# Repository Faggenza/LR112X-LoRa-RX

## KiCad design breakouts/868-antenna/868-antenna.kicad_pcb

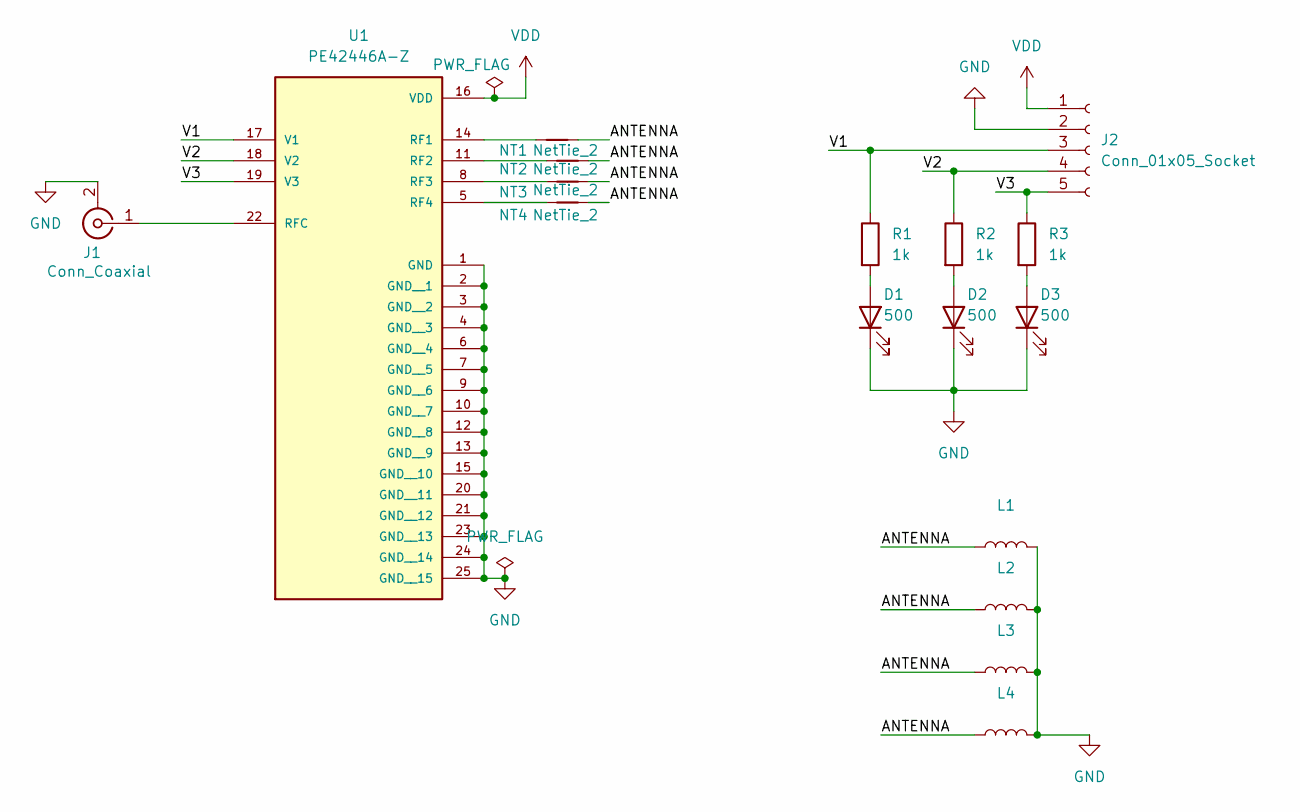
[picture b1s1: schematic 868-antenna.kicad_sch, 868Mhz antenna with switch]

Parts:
D1, D2, D3: 500; LED_0805_2012Metric_Pad1.15x1.40mm_HandSolder
J1: Conn_Coaxial; SMA_Amphenol_901-144_Vertical
J2: Conn_01x05_Socket; PinSocket_1x05_P2.54mm_Vertical
L1, L2, L3, L4: L_0805_2012Metric_Pad1.05x1.20mm_HandSolder
NT1, NT2, NT3, NT4: NetTie_2; NetTie-2_SMD_Pad0.5mm
R1, R2, R3: 1k; R_0805_2012Metric_Pad1.20x1.40mm_HandSolder
U1: PE42446A-Z; IC_PE42446A-Z; PARTREV 08/2024

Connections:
/ANTENNA: L1.1, L2.1, L3.1, L4.1, NT1.2, NT2.2, NT3.2, NT4.2
/V1: J2.3, R1.1, U1.17 (V1)
/V2: J2.4, R2.1, U1.18 (V2)
/V3: J2.5, R3.1, U1.19 (V3)
GND: D1.1 (K), D2.1 (K), D3.1 (K), J1.2 (Ext), J2.2, L1.2, L2.2, L3.2, L4.2, U1.1 (GND), U1.2 (GND__1), U1.3 (GND__2), U1.4 (GND__3), U1.6 (GND__4), U1.7 (GND__5), U1.9 (GND__6), U1.10 (GND__7), U1.12 (GND__8), U1.13 (GND__9), U1.15 (GND__10), U1.20 (GND__11), U1.21 (GND__12), U1.23 (GND__13), U1.24 (GND__14), U1.25 (GND__15)
unnamed: D1.2 (A), R1.2
unnamed: D2.2 (A), R2.2
unnamed: D3.2 (A), R3.2
unnamed: J1.1 (In), U1.22 (RFC)
unnamed: NT1.1, U1.14 (RF1)
unnamed: NT2.1, U1.11 (RF2)
unnamed: NT3.1, U1.8 (RF3)
unnamed: NT4.1, U1.5 (RF4)
VDD: J2.1, U1.16 (VDD)

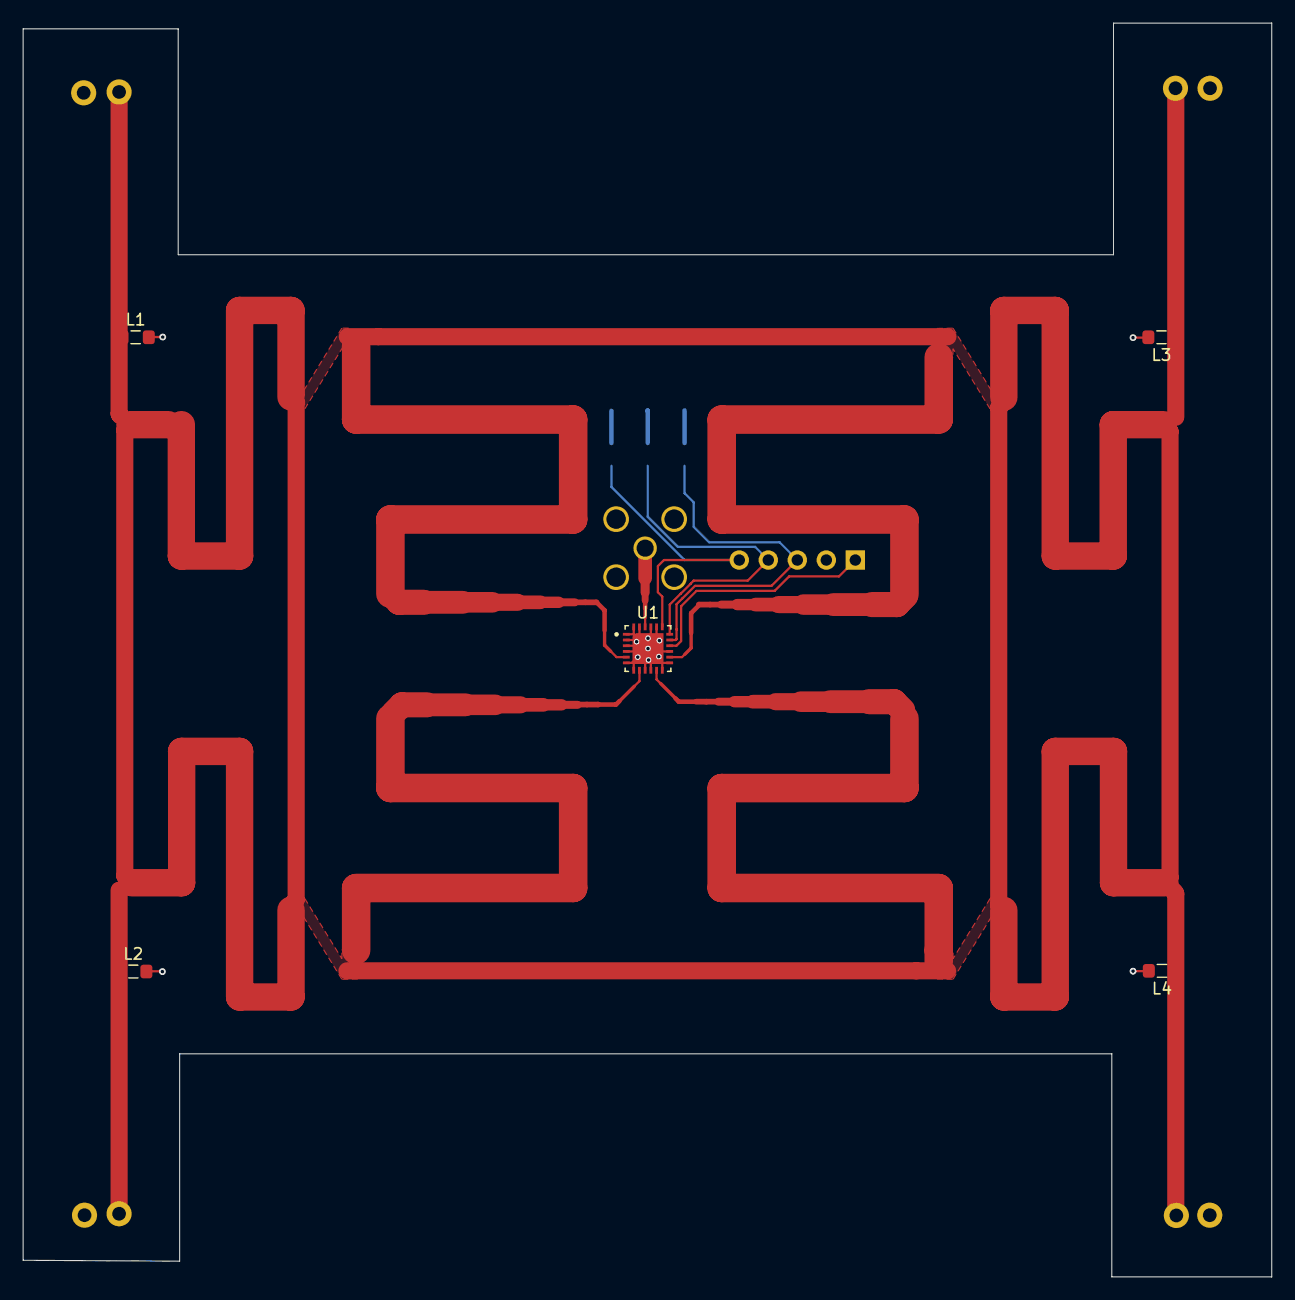
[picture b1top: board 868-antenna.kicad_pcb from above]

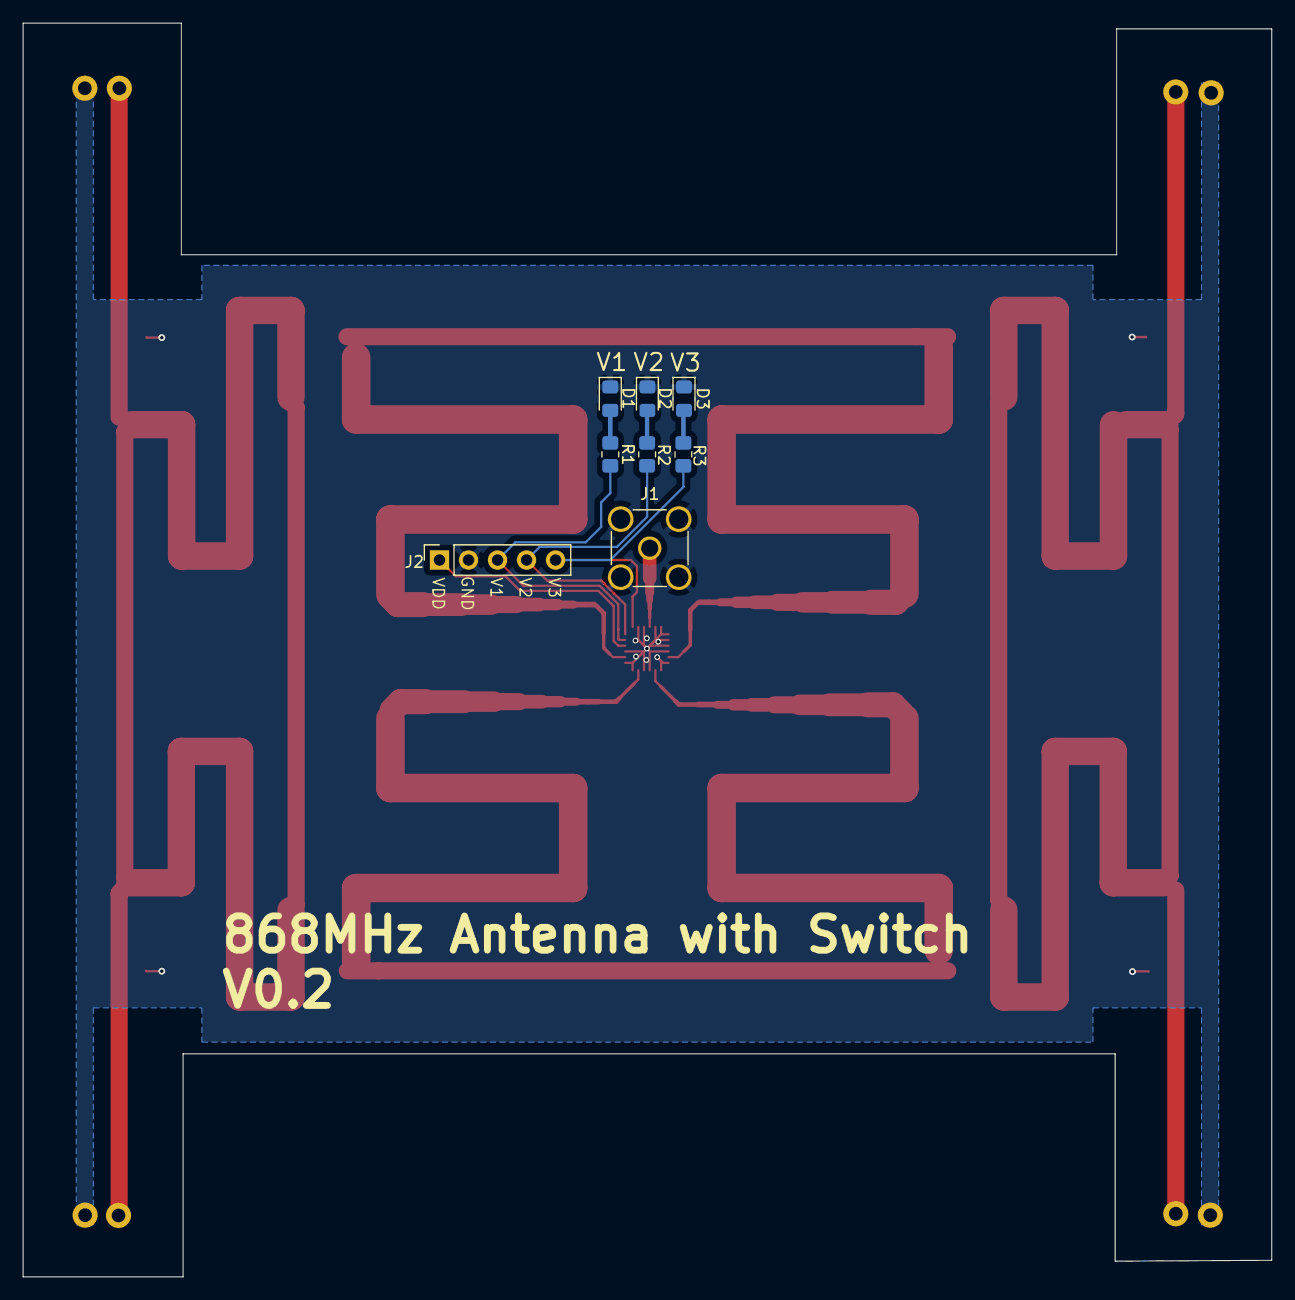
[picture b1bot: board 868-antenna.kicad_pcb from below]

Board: 2 copper layers, 109.3 x 109.8 mm, 17 parts (8 on the bottom side), 14 nets.

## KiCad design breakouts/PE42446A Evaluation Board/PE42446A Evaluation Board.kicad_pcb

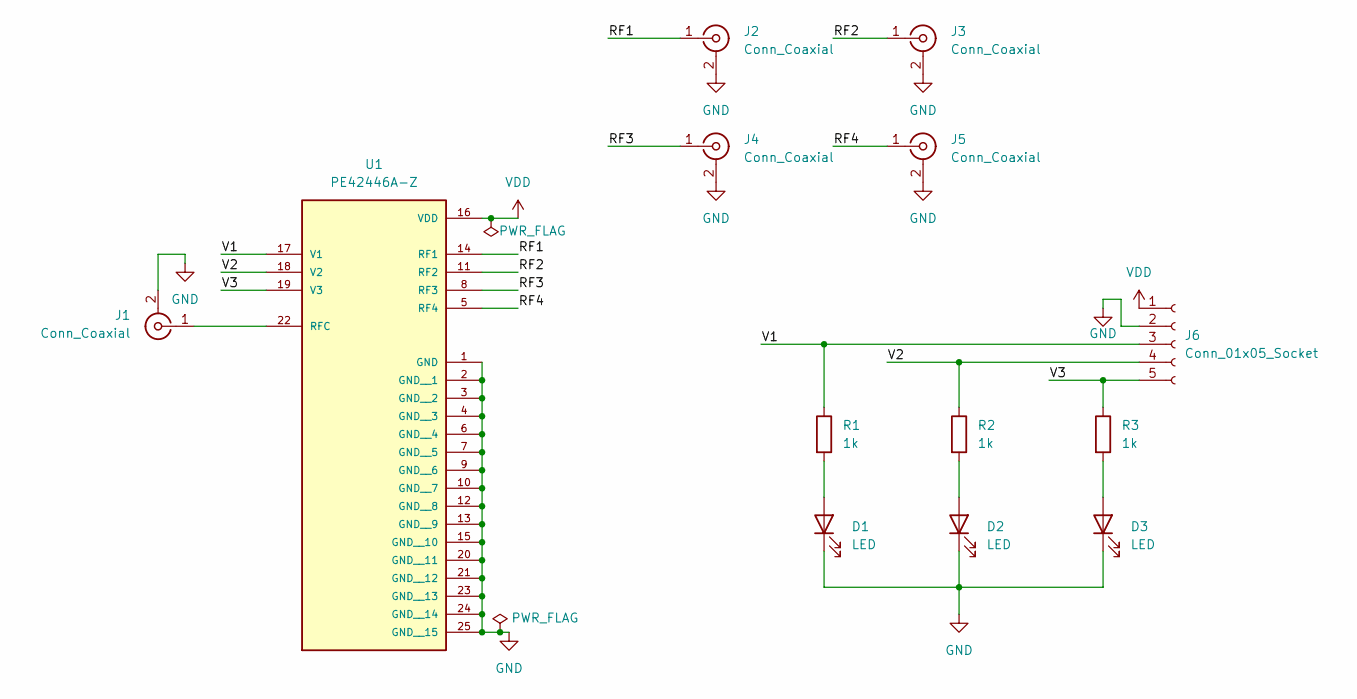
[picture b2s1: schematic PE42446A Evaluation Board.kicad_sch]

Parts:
D1, D2, D3: LED; LED_0805_2012Metric_Pad1.15x1.40mm_HandSolder
J1, J2, J3, J4, J5: Conn_Coaxial; SMA_Molex_73251-1153_EdgeMount_Horizontal
J6: Conn_01x05_Socket; PinSocket_1x05_P2.54mm_Vertical
R1, R2, R3: 1k; R_0805_2012Metric_Pad1.20x1.40mm_HandSolder
U1: PE42446A-Z; IC_PE42446A-Z; PARTREV 08/2024

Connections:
/RF1: J2.1 (In), U1.14 (RF1)
/RF2: J3.1 (In), U1.11 (RF2)
/RF3: J4.1 (In), U1.8 (RF3)
/RF4: J5.1 (In), U1.5 (RF4)
/V1: J6.3, R1.1, U1.17 (V1)
/V2: J6.4, R2.1, U1.18 (V2)
/V3: J6.5, R3.1, U1.19 (V3)
GND: D1.1 (K), D2.1 (K), D3.1 (K), J1.2 (Ext), J2.2 (Ext), J3.2 (Ext), J4.2 (Ext), J5.2 (Ext), J6.2, U1.1 (GND), U1.2 (GND__1), U1.3 (GND__2), U1.4 (GND__3), U1.6 (GND__4), U1.7 (GND__5), U1.9 (GND__6), U1.10 (GND__7), U1.12 (GND__8), U1.13 (GND__9), U1.15 (GND__10), U1.20 (GND__11), U1.21 (GND__12), U1.23 (GND__13), U1.24 (GND__14), U1.25 (GND__15)
unnamed: D1.2 (A), R1.2
unnamed: D2.2 (A), R2.2
unnamed: D3.2 (A), R3.2
unnamed: J1.1 (In), U1.22 (RFC)
VDD: J6.1, U1.16 (VDD)

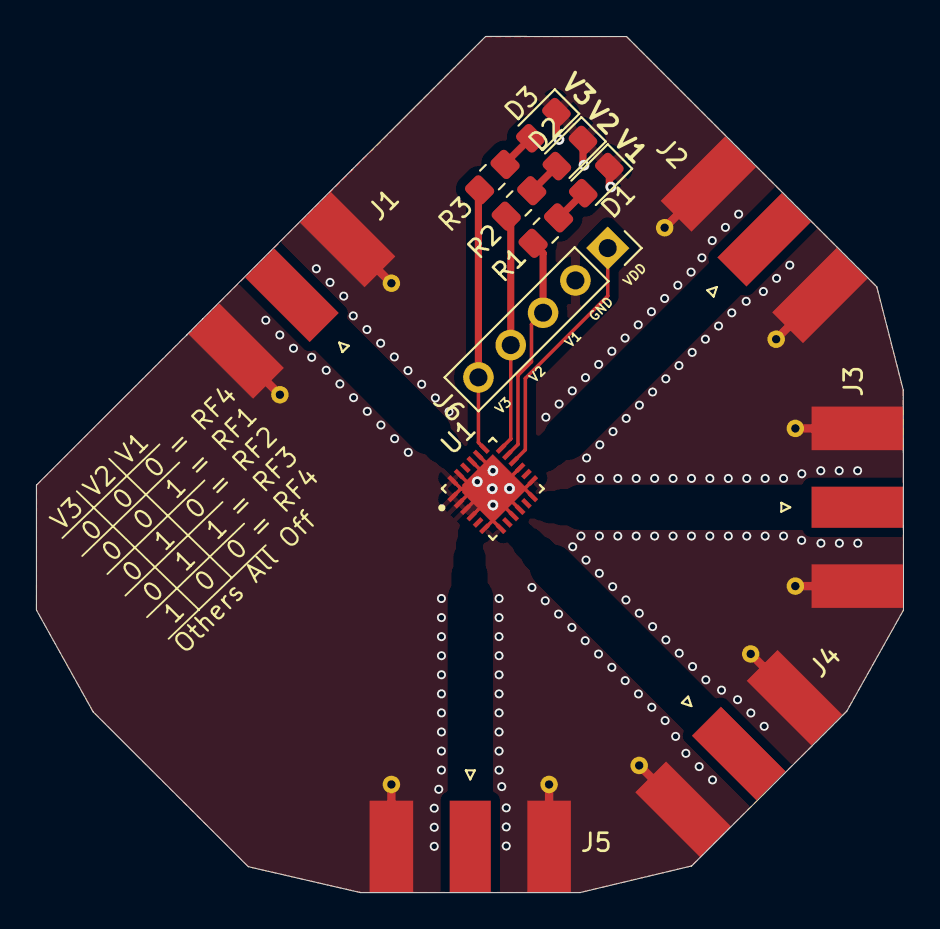
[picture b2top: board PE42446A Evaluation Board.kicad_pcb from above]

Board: 2 copper layers, 48.2 x 47.6 mm, 13 parts (0 on the bottom side), 13 nets.

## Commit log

2026-03-20 hw: brakouts antenna and evaluation board
2026-03-20 fw: init
2026-03-20 docs
2026-03-23 fw: init rx. we get packages
2026-03-24 fw: python for testing
